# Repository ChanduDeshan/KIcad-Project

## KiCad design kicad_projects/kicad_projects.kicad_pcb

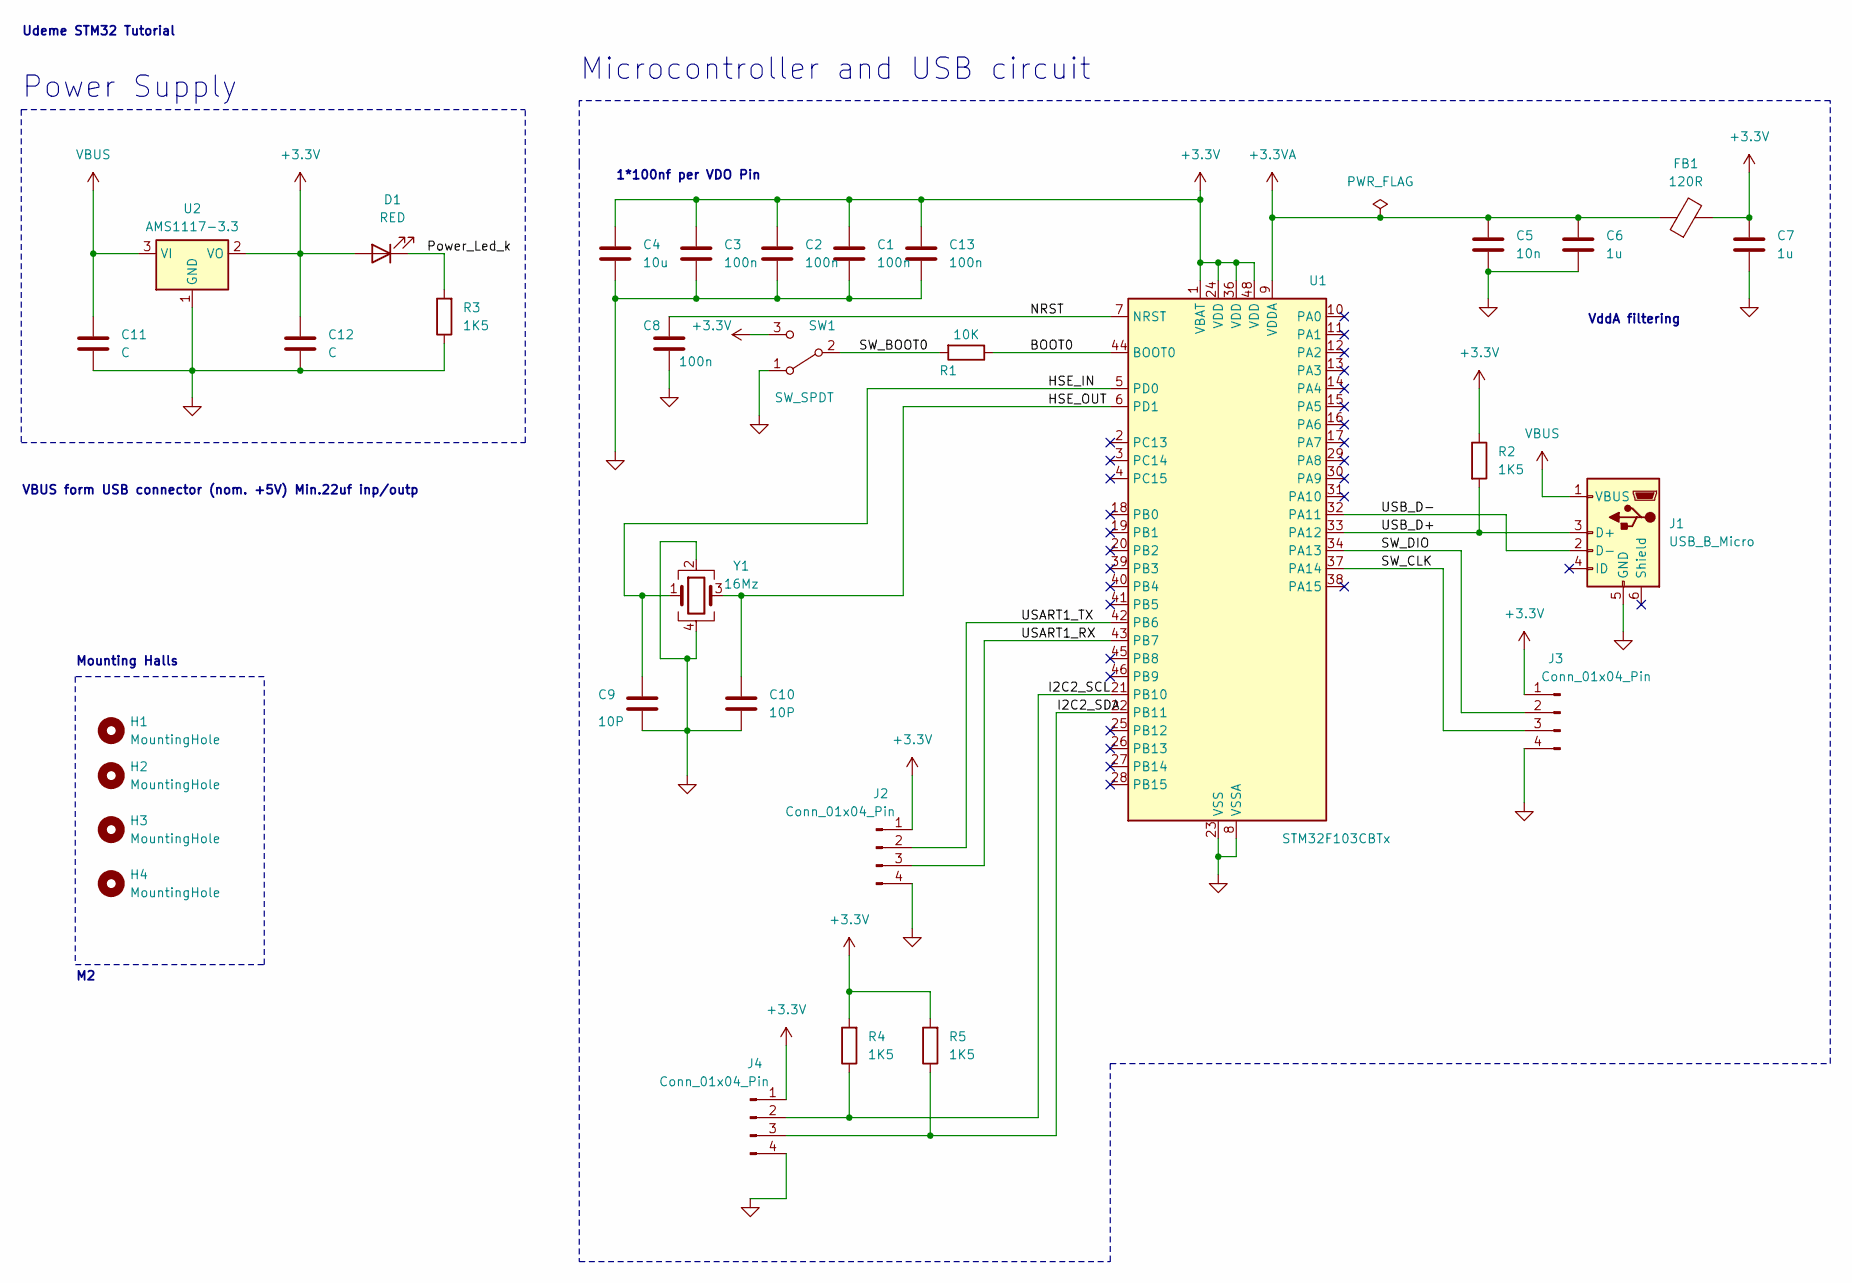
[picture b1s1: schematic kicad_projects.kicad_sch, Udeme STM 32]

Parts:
C1, C2, C3, C8, C13: 100n; C_0402_1005Metric
C4: 10u; C_0603_1608Metric_Pad1.08x0.95mm_HandSolder
C5: 10n; C_0603_1608Metric
C6: 1u; C_0402_1005Metric_Pad0.74x0.62mm_HandSolder
C7: 1u; C_0402_1005Metric
C9, C10: 10P; C_0402_1005Metric
C11, C12: C; C_0805_2012Metric
D1: RED; LED_0603_1608Metric
FB1: 120R; L_0603_1608Metric
H1, H2, H3, H4: MountingHole; MountingHole_2.2mm_M2
J1: USB_B_Micro; USB_Micro-B_Wuerth_629105150521
J2, J3, J4: Conn_01x04_Pin; JST_EH_B4B-EH-A_1x04_P2.50mm_Vertical
R1: 10K; R_0402_1005Metric
R2, R3, R4, R5: 1K5; R_0402_1005Metric
SW1: SW_SPDT; SW_SPDT_CK-JS102011SAQN
U1: STM32F103CBTx; LQFP-48_7x7mm_P0.5mm
U2: AMS1117-3.3; SOT-223-3_TabPin2
Y1: 16Mz; Crystal_SMD_3225-4Pin_3.2x2.5mm

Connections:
+3.3V: C1.1, C2.1, C3.1, C4.1, C7.1, C12.1, C13.1, D1.2 (A), FB1.2, J2.1, J3.1, J4.1, R2.1, R4.2, R5.2, SW1.3 (C), U1.1 (VBAT), U1.24 (VDD), U1.36 (VDD), U1.48 (VDD), U2.2 (VO)
+3.3VA: C5.1, C6.1, FB1.1, U1.9 (VDDA)
/BOOT0: R1.1, U1.44 (BOOT0)
/HSE_IN: C9.1, U1.5 (PD0), Y1.1
/HSE_OUT: C10.1, U1.6 (PD1), Y1.3
/I2C2_SCL: J4.2, R4.1, U1.21 (PB10)
/I2C2_SDA: J4.3, R5.1, U1.22 (PB11)
/NRST: C8.1, U1.7 (NRST)
/Power_Led_k: D1.1 (K), R3.2
/SW_BOOT0: R1.2, SW1.2 (B)
/SW_CLK: J3.3, U1.37 (PA14)
/SW_DIO: J3.2, U1.34 (PA13)
/USART1_RX: J2.3, U1.43 (PB7)
/USART1_TX: J2.2, U1.42 (PB6)
/USB_D+: J1.3 (D+), R2.2, U1.33 (PA12)
/USB_D-: J1.2 (D-), U1.32 (PA11)
GND: C1.2, C2.2, C3.2, C4.2, C5.2, C6.2, C7.2, C8.2, C9.2, C10.2, C11.2, C12.2, C13.2, J1.5 (GND), J2.4, J3.4, J4.4, R3.1, SW1.1 (A), U1.8 (VSSA), U1.23 (VSS), U1.35 (VSS), U1.47 (VSS), U2.1 (GND), Y1.2, Y1.4
VBUS: C11.1, J1.1 (VBUS), U2.3 (VI)

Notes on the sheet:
1*100nf per VDO Pin
Microcontroller and USB circuit
Mounting Halls
Udeme STM32 Tutorial
VBUS form USB connector (nom. +5V) Min.22uf inp/outp
VddA filtering
Power Supply

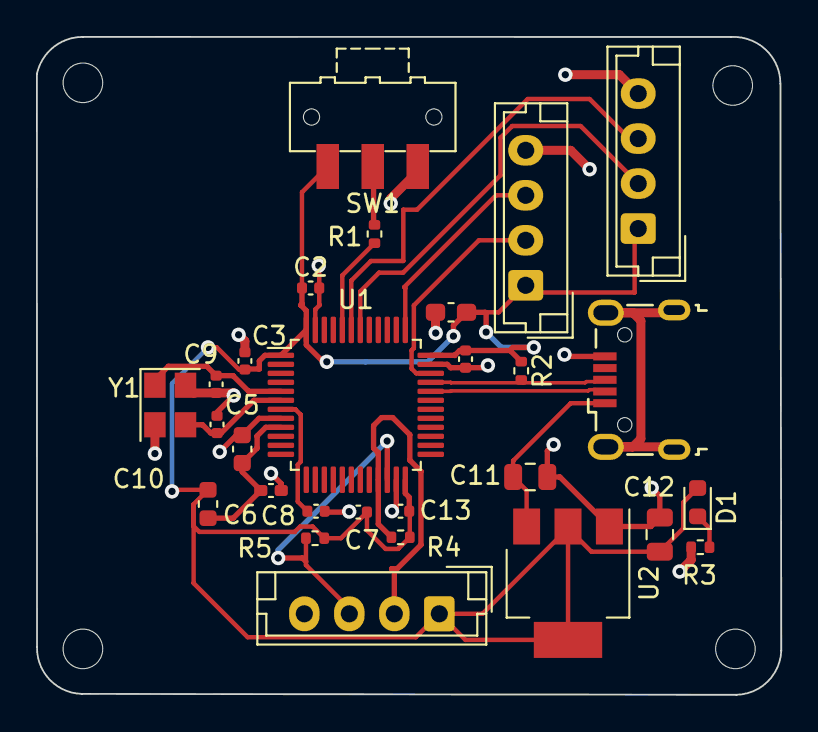
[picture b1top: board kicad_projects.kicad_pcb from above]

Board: 2 copper layers, 41.4 x 36.5 mm, 32 parts (0 on the bottom side), 18 nets.
